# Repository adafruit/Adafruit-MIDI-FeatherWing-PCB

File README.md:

## Adafruit MIDI FeatherWing Kit PCB

<a href="http://www.adafruit.com/products/4740"><br/>
Click here to purchase one from the Adafruit shop</a>

PCB files for the Adafruit MIDI FeatherWing Kit.

Format is EagleCAD schematic and board layout
* https://www.adafruit.com/product/4740

### Description

Turn your Feather into a song-bird with this musically-enabled FeatherWing that adds MIDI input and output jacks to just about any Feather. You get both input and output DIN-5 MIDI jacks, a 3V optically isolator so you can interface with MIDI on 3.3V logic/power microcontrollers, and two blinky indicator LEDs underneath the jacks to help you know when data is sent and received.

For those who have moved from DIN-5 jacks to "TRS MIDI A" 3.5mm jacks, we provide spots to solder in 3.5mm stereo jacks (optional and not included by default)

We use the hardware serial pins RX and TX to send/receive data - you'll need to set these to 31250 baud in your programming language and then send/receive MIDI packet data. For example, here's how you would do it in Arduino or a full-featured library with helpers. Here's an example on using a UART for MIDI transport in CircuitPython.

Because we use the UART, this works with all Feathers except for those with USB-Serial converters that use the UART pins. Right now that means the ESP8266 Huzzah Feather, 328p Feather and nRF52 Feather don't work because they use the hardware UART for programming. Any other Feathers with native USB will work just fine.

Comes as a kit with an assembled PCB that has all the surface-mount components attached, loose headers, and two loose DIN-5 jacks. Some basic soldering is required to assemble the header and DIN jacks in place. If you're like to use 3.5mm jacks, you'll want to pick up some through-hole 3.5mm stereo jacks and solder those in, instead.

### License

Adafruit invests time and resources providing this open source design, please support Adafruit and open-source hardware by purchasing products from [Adafruit](https://www.adafruit.com)!

Designed by Limor Fried/Ladyada for Adafruit Industries.

Creative Commons Attribution/Share-Alike, all text above must be included in any redistribution.
See license.txt for additional details.

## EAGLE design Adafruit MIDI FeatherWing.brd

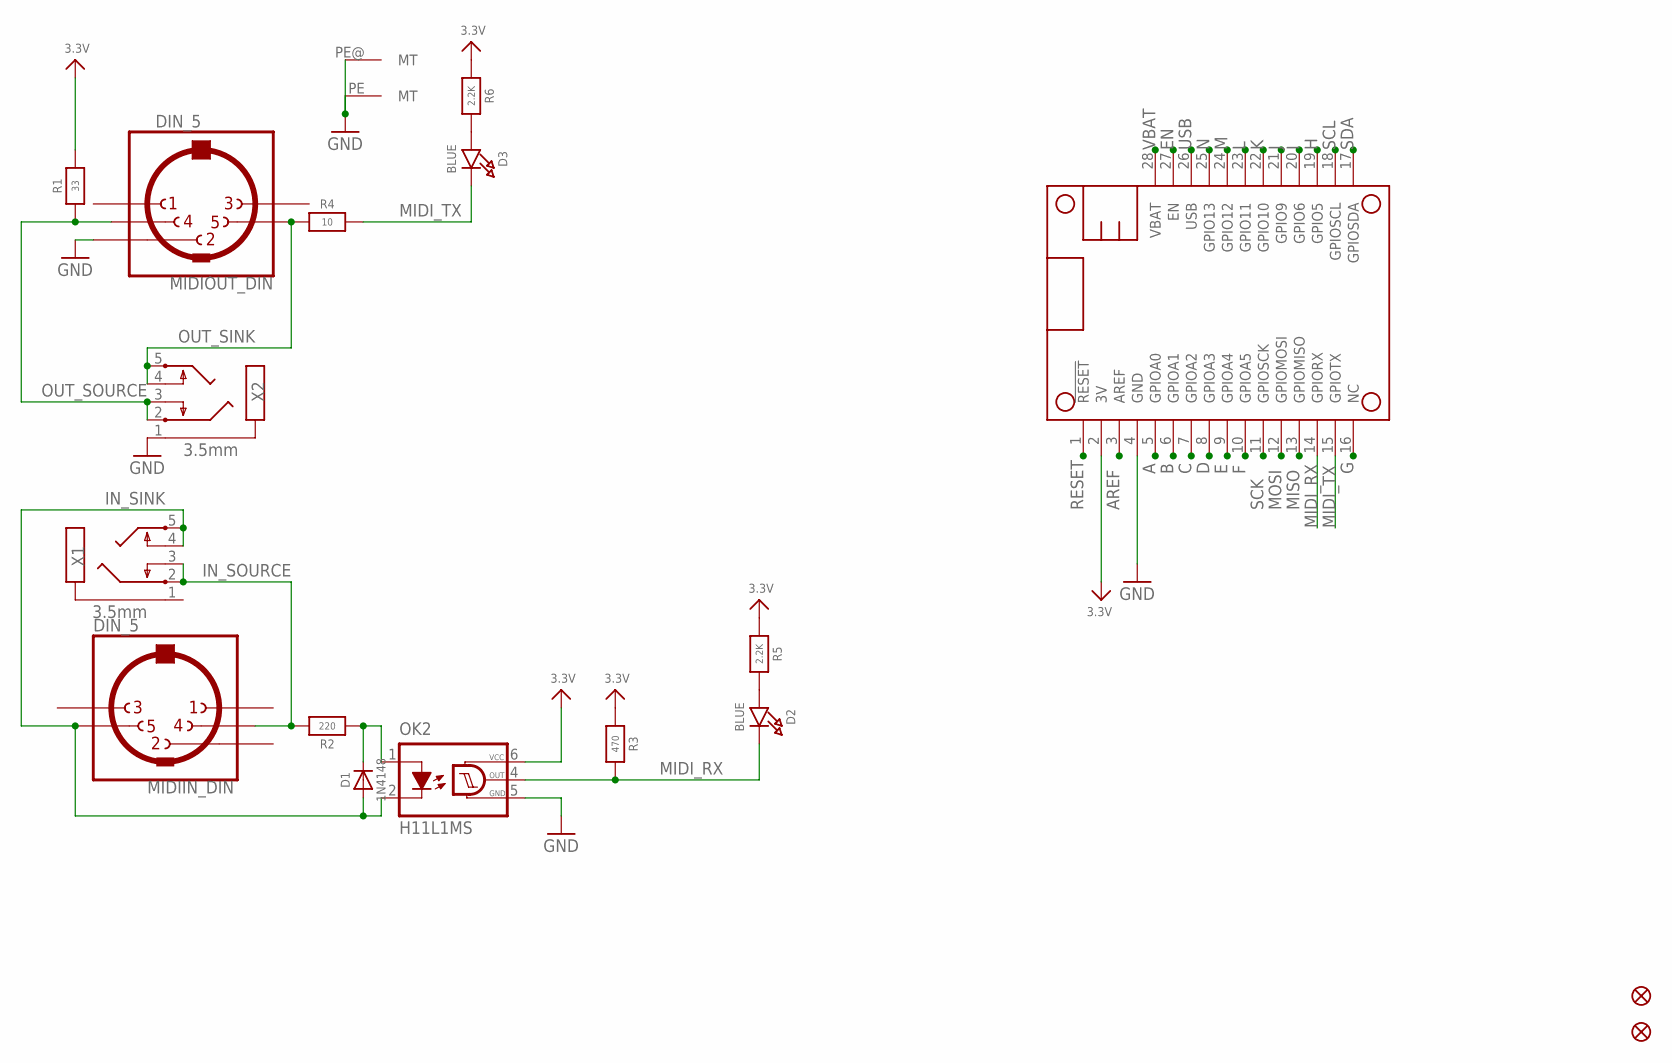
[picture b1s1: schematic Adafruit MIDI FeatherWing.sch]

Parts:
D1: 1N4148; SOD-323
D2, D3: BLUE; CHIPLED_0603
FID1, FID2: FIDUCIAL_1MM
MIDIIN: DIN_5; CP-2350
MIDIOUT: DIN_5; CP-2350
MS1: FEATHERWING_NODIM
OK2: H11L1MS; DIL6-SMD
R1: 33; 0603-NO
R2: 220; 0603-NO
R3: 470; 0603-NO
R4: 10; 0603-NO
R5, R6: 2.2K; 0603-NO
X1, X2: 3.5mm; STX3100

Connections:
3.3V: MS1.2 (3V), OK2.6 (VCC), R1.2, R3.1, R5.1, R6.1
A: MS1.5 (GPIOA0)
AREF: MS1.3 (AREF)
B: MS1.6 (GPIOA1)
C: MS1.7 (GPIOA2)
D: MS1.8 (GPIOA3)
E: MS1.9 (GPIOA4)
EN: MS1.27 (EN)
F: MS1.10 (GPIOA5)
G: MS1.16 (NC)
GND: MIDIOUT.2, MIDIOUT.PE (MT), MIDIOUT.PE@ (MT), MS1.4 (GND), OK2.5 (GND), X2.1
H: MS1.19 (GPIO5)
I: MS1.20 (GPIO6)
IN_SINK: D1.A, MIDIIN.5, OK2.2 (C), X1.4, X1.5
IN_SOURCE: MIDIIN.4, R2.2, X1.2, X1.3
J: MS1.21 (GPIO9)
K: MS1.22 (GPIO10)
L: MS1.23 (GPIO11)
M: MS1.24 (GPIO12)
MIDI_RX: D2.C, MS1.14 (GPIORX), OK2.4 (OUT), R3.2
MIDI_TX: D3.C, MS1.15 (GPIOTX), R4.2
MISO: MS1.13 (GPIOMISO)
MOSI: MS1.12 (GPIOMOSI)
N: MS1.25 (GPIO13)
unnamed: D2.A, R5.2
unnamed: D3.A, R6.2
unnamed: D1.C, OK2.1 (A), R2.1
OUT_SINK: MIDIOUT.5, R4.1, X2.4, X2.5
OUT_SOURCE: MIDIOUT.4, R1.1, X2.2, X2.3
RESET: MS1.1 (!RESET)
SCK: MS1.11 (GPIOSCK)
SCL: MS1.18 (GPIOSCL)
SDA: MS1.17 (GPIOSDA)
USB: MS1.26 (USB)
VBAT: MS1.28 (VBAT)

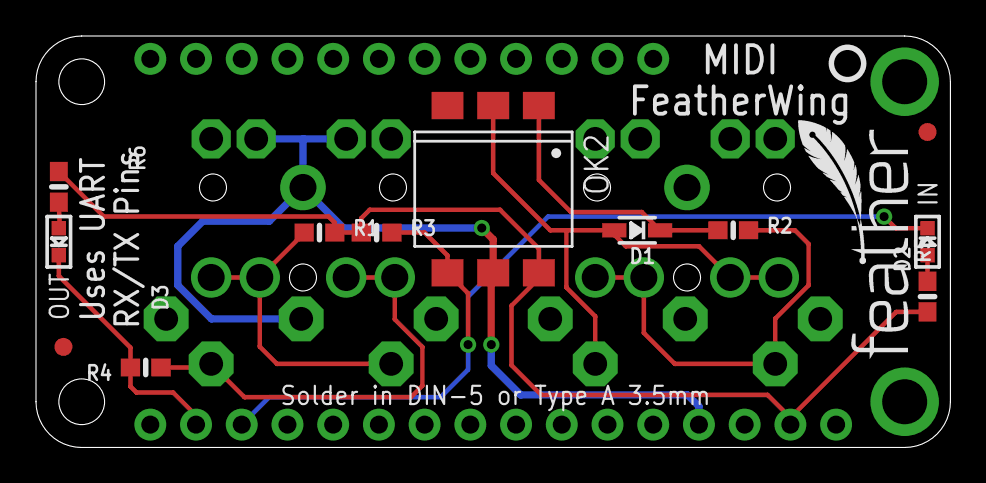
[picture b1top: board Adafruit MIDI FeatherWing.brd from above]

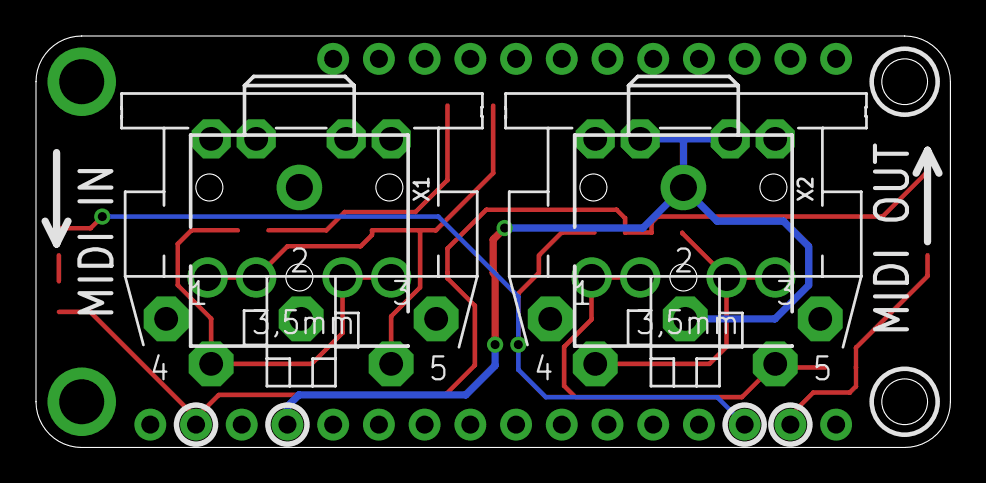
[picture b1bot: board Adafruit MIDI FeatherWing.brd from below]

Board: 2 copper layers, 50.8 x 22.9 mm, 19 parts (5 on the bottom side), 11 nets.

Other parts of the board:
U$8: PCBFEAT-REV-040
U$9: FEATHERLOGO_SMALL

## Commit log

2020-09-30 Adding board files.

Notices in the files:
parts and their libraries:
microbuilder: This work is placed in the public domain, and may be freely used for commercial and non-commercial work with the following conditions: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
microbuilder: Shamelessly taken from the Adafruit Eagle library (public domain) ... thanks!
